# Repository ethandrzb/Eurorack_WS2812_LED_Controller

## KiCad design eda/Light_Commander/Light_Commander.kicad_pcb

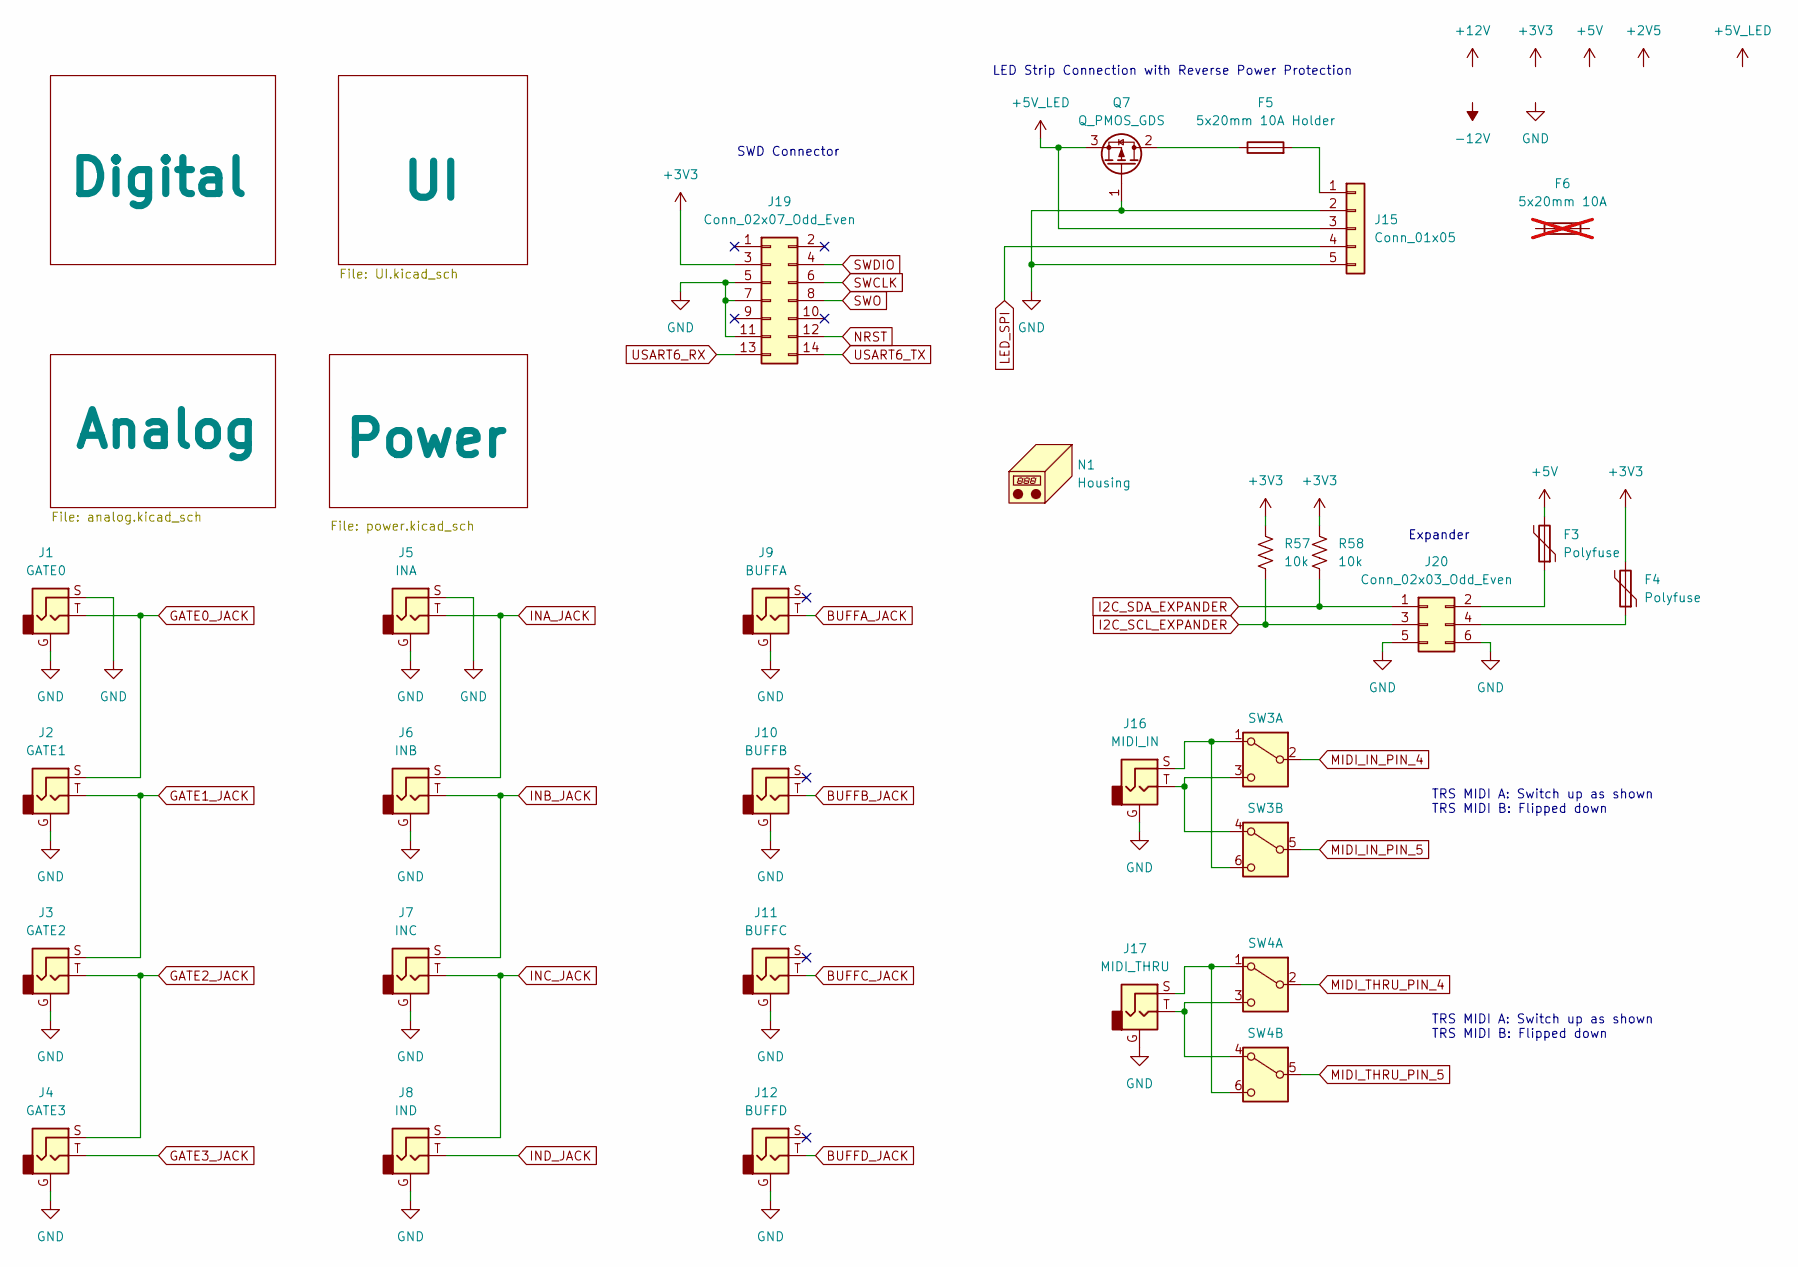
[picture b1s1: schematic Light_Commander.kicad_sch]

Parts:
F3, F4: Polyfuse; Fuse_0805_2012Metric; Digikey_PN 13-SMDH0805B010TFCT-ND
F5: 5x20mm 10A Holder; 05200101Z; Digikey_PN F1504-ND
F6: 5x20mm 10A; Digikey_PN 0617010.MXP-ND; not fitted
J1: GATE0; PJ301M-12
J2: GATE1; PJ301M-12
J3: GATE2; PJ301M-12
J4: GATE3; PJ301M-12
J5: INA; PJ301M-12
J6: INB; PJ301M-12
J7: INC; PJ301M-12
J8: IND; PJ301M-12
J9: BUFFA; PJ301M-12
J10: BUFFB; PJ301M-12
J11: BUFFC; PJ301M-12
J12: BUFFD; PJ301M-12
J15: Conn_01x05; CUI_TBLH10V-350-05BK; Digikey_PN 102-TBLH10V-350-05BK-ND
J16: MIDI_IN; PJ301M-12_STEREO
J17: MIDI_THRU; PJ301M-12_STEREO
J19: Conn_02x07_Odd_Even; SAMTEC_FTSH-107-01-L-DV-K-A; Digikey_PN FTSH-107-01-L-DV-K-A-ND
J20: Conn_02x03_Odd_Even; IDC-Header_2x03_P2.54mm_Vertical; Digikey_PN S9716-ND
N1: Housing; Light_Commander_Panel
Q7: Q_PMOS_GDS; TO-252-2; Digikey_PN 4786-SSFD6909CT-ND
R57, R58: 10k; R_0805_2012Metric; Digikey_PN 311-10.0KCRCT-ND
SW3, SW4: SW_DPDT_x2; CAS-220TA; Digikey_PN CAS220JCT-ND

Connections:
+3V3: F4.2, J19.3, R57.1, R58.1; also elsewhere on the board
+5V: F3.2; also elsewhere on the board
+5V_LED: J15.3, Q7.3 (S); also elsewhere on the board
BUFFA_JACK: J9.T; also elsewhere on the board
BUFFB_JACK: J10.T; also elsewhere on the board
BUFFC_JACK: J11.T; also elsewhere on the board
BUFFD_JACK: J12.T; also elsewhere on the board
GATE0_JACK: J1.T, J2.S; also elsewhere on the board
GATE1_JACK: J2.T, J3.S; also elsewhere on the board
GATE2_JACK: J3.T, J4.S; also elsewhere on the board
GATE3_JACK: J4.T; also elsewhere on the board
GND: J1.G, J1.S, J2.G, J3.G, J4.G, J5.G, J5.S, J6.G, J7.G, J8.G, J9.G, J10.G, J11.G, J12.G, J15.2, J15.5, J16.G, J17.G, J19.5, J19.7, J19.11, J20.5, J20.6, Q7.1 (G); also elsewhere on the board
I2C_SCL_EXPANDER: J20.3, R57.2; also elsewhere on the board
I2C_SDA_EXPANDER: J20.1, R58.2; also elsewhere on the board
INA_JACK: J5.T, J6.S; also elsewhere on the board
INB_JACK: J6.T, J7.S; also elsewhere on the board
INC_JACK: J7.T, J8.S; also elsewhere on the board
IND_JACK: J8.T; also elsewhere on the board
LED_SPI: J15.4; also elsewhere on the board
MIDI_IN_PIN_4: SW3.2 (B); also elsewhere on the board
MIDI_IN_PIN_5: SW3.5 (B); also elsewhere on the board
MIDI_THRU_PIN_4: SW4.2 (B); also elsewhere on the board
MIDI_THRU_PIN_5: SW4.5 (B); also elsewhere on the board
NRST: J19.12; also elsewhere on the board
unnamed: F5.2, J15.1
unnamed: F3.1, J20.2
unnamed: F4.1, J20.4
unnamed: F5.1, Q7.2 (D)
unnamed: J16.S, SW3.1 (A), SW3.6 (C)
unnamed: J16.T, SW3.3 (C), SW3.4 (A)
unnamed: J17.S, SW4.1 (A), SW4.6 (C)
unnamed: J17.T, SW4.3 (C), SW4.4 (A)
SWCLK: J19.6; also elsewhere on the board
SWDIO: J19.4; also elsewhere on the board
SWO: J19.8; also elsewhere on the board
USART6_RX: J19.13; also elsewhere on the board
USART6_TX: J19.14; also elsewhere on the board

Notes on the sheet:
TRS MIDI A: Switch up as shown TRS MIDI B: Flipped down
Expander
SWD Connector
LED Strip Connection with Reverse Power Protection

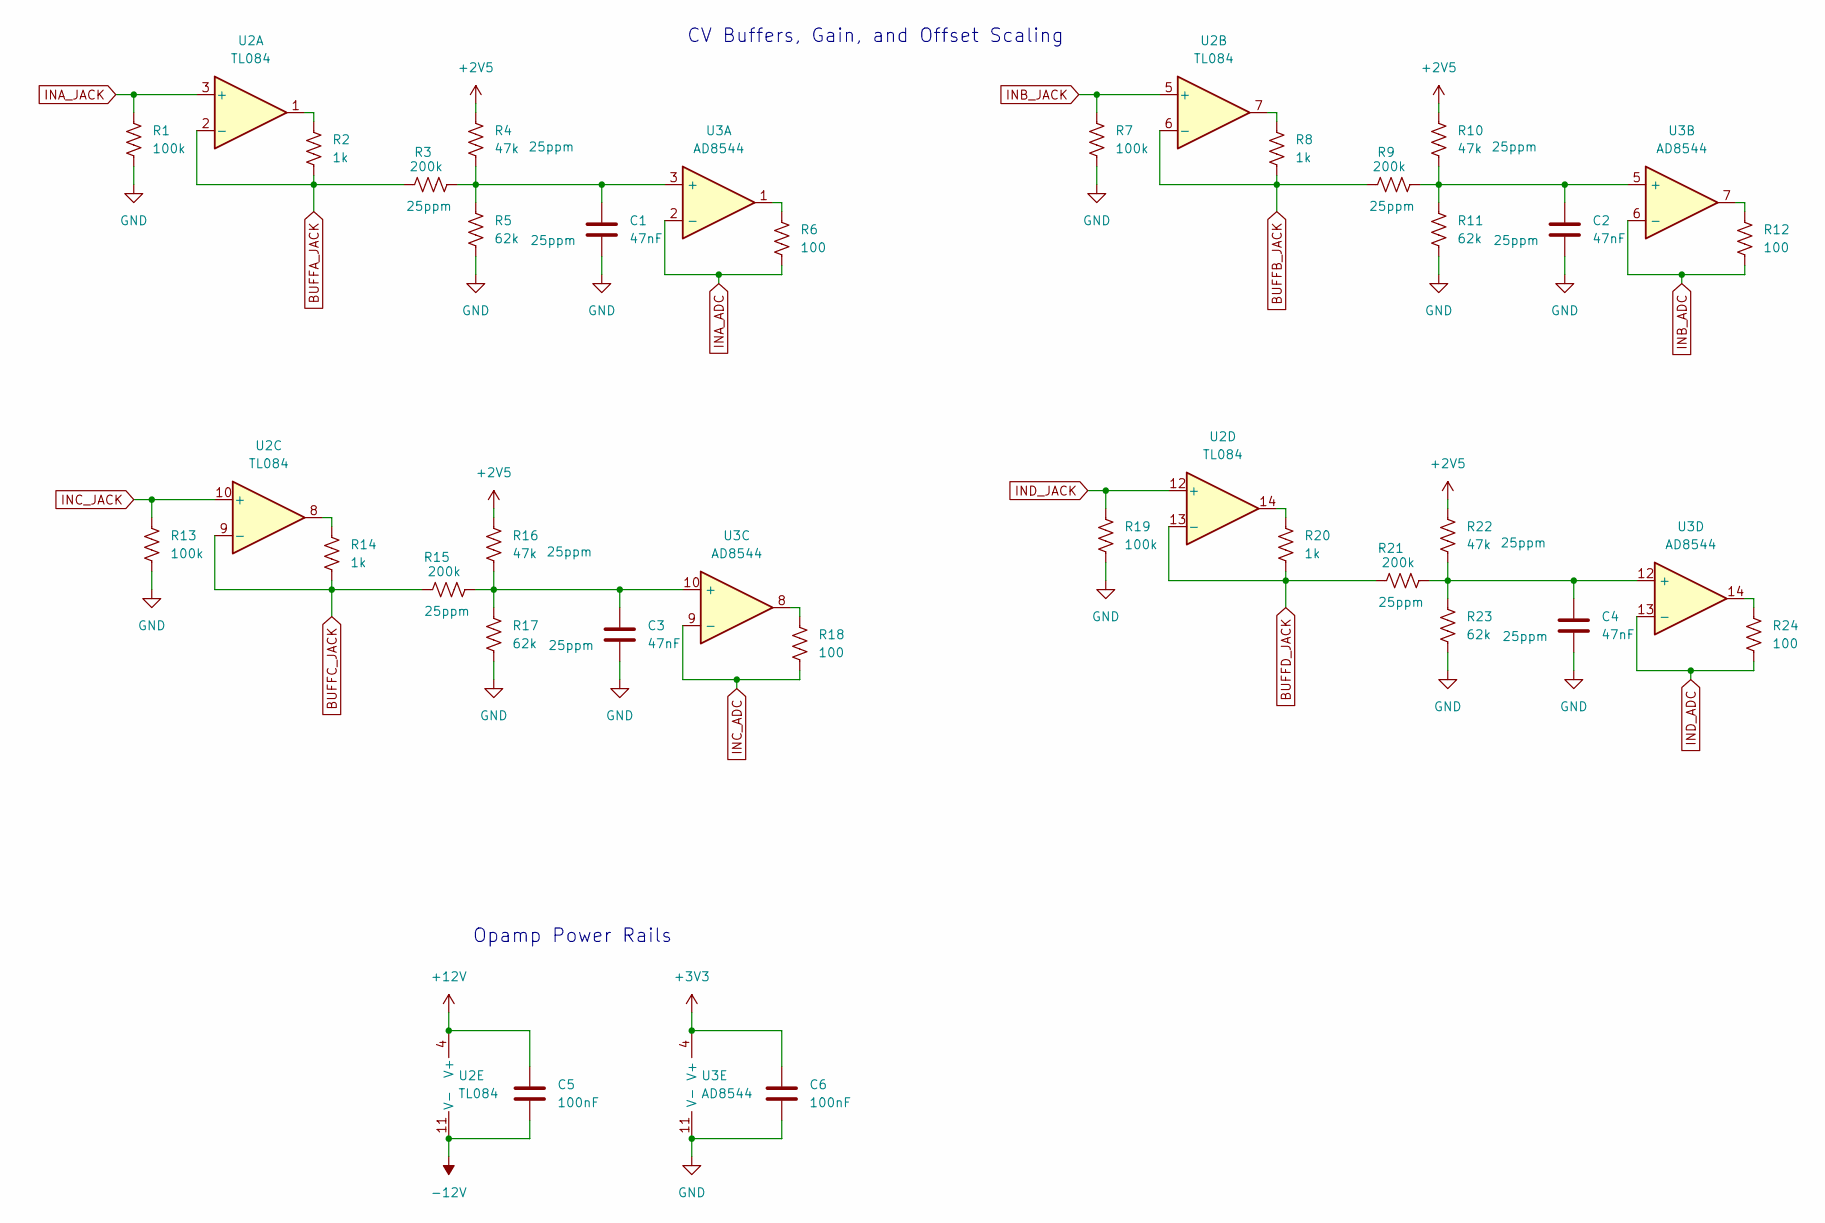
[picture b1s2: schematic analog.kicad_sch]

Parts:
C1, C2, C3, C4: 47nF; C_0805_2012Metric; Digikey_PN 399-C0805C473J3GECTUCT-ND
C5, C6: 100nF; C_0805_2012Metric; Digikey_PN 1276-1003-1-ND
R1, R7, R13, R19: 100k; R_0805_2012Metric; Digikey_PN 311-100KCRCT-ND
R2, R8, R14, R20: 1k; R_0805_2012Metric; Digikey_PN 541-1.00KCCT-ND
R3, R9, R15, R21: 200k; R_0805_2012Metric; Digikey_PN RG20P200KBCT-ND
R4, R10, R16, R22: 47k; R_0805_2012Metric; Digikey_PN RG20P47.0KBCT-ND
R5, R11, R17, R23: 62k; R_0805_2012Metric; Digikey_PN P62KDACT-ND
R6, R12, R18, R24: 100; R_0805_2012Metric; Digikey_PN 311-100CRCT-ND
U2: TL084; SOIC-14_3.9x8.7mm_P1.27mm; Digikey_PN 296-TL084HIDRCT-ND
U3: AD8544; SOIC-14_3.9x8.7mm_P1.27mm; Digikey_PN AD8544ARZ-REELCT-ND

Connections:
+2V5: R4.1, R10.1, R16.1, R22.1; also elsewhere on the board
+3V3: C6.1, U3.4 (V+); also elsewhere on the board
+12V: C5.1, U2.4 (V+); also elsewhere on the board
-12V: C5.2, U2.11 (V-); also elsewhere on the board
BUFFA_JACK: R2.2, R3.1, U2.2 (-); also elsewhere on the board
BUFFB_JACK: R8.2, R9.1, U2.6 (-); also elsewhere on the board
BUFFC_JACK: R14.2, R15.1, U2.9 (-); also elsewhere on the board
BUFFD_JACK: R20.2, R21.1, U2.13 (-); also elsewhere on the board
GND: C1.2, C2.2, C3.2, C4.2, C6.2, R1.2, R5.2, R7.2, R11.2, R13.2, R17.2, R19.2, R23.2, U3.11 (V-); also elsewhere on the board
INA_ADC: R6.1, U3.2 (-); also elsewhere on the board
INA_JACK: R1.1, U2.3 (+); also elsewhere on the board
INB_ADC: R12.1, U3.6 (-); also elsewhere on the board
INB_JACK: R7.1, U2.5 (+); also elsewhere on the board
INC_ADC: R18.1, U3.9 (-); also elsewhere on the board
INC_JACK: R13.1, U2.10 (+); also elsewhere on the board
IND_ADC: R24.1, U3.13 (-); also elsewhere on the board
IND_JACK: R19.1, U2.12 (+); also elsewhere on the board
unnamed: R2.1, U2.1
unnamed: R6.2, U3.1
unnamed: R8.1, U2.7
unnamed: R12.2, U3.7
unnamed: R14.1, U2.8
unnamed: R18.2, U3.8
unnamed: R20.1, U2.14
unnamed: R24.2, U3.14
unnamed: C1.1, R3.2, R4.2, R5.1, U3.3 (+)
unnamed: C2.1, R9.2, R10.2, R11.1, U3.5 (+)
unnamed: C3.1, R15.2, R16.2, R17.1, U3.10 (+)
unnamed: C4.1, R21.2, R22.2, R23.1, U3.12 (+)

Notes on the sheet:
CV Buffers, Gain, and Offset Scaling
Opamp Power Rails

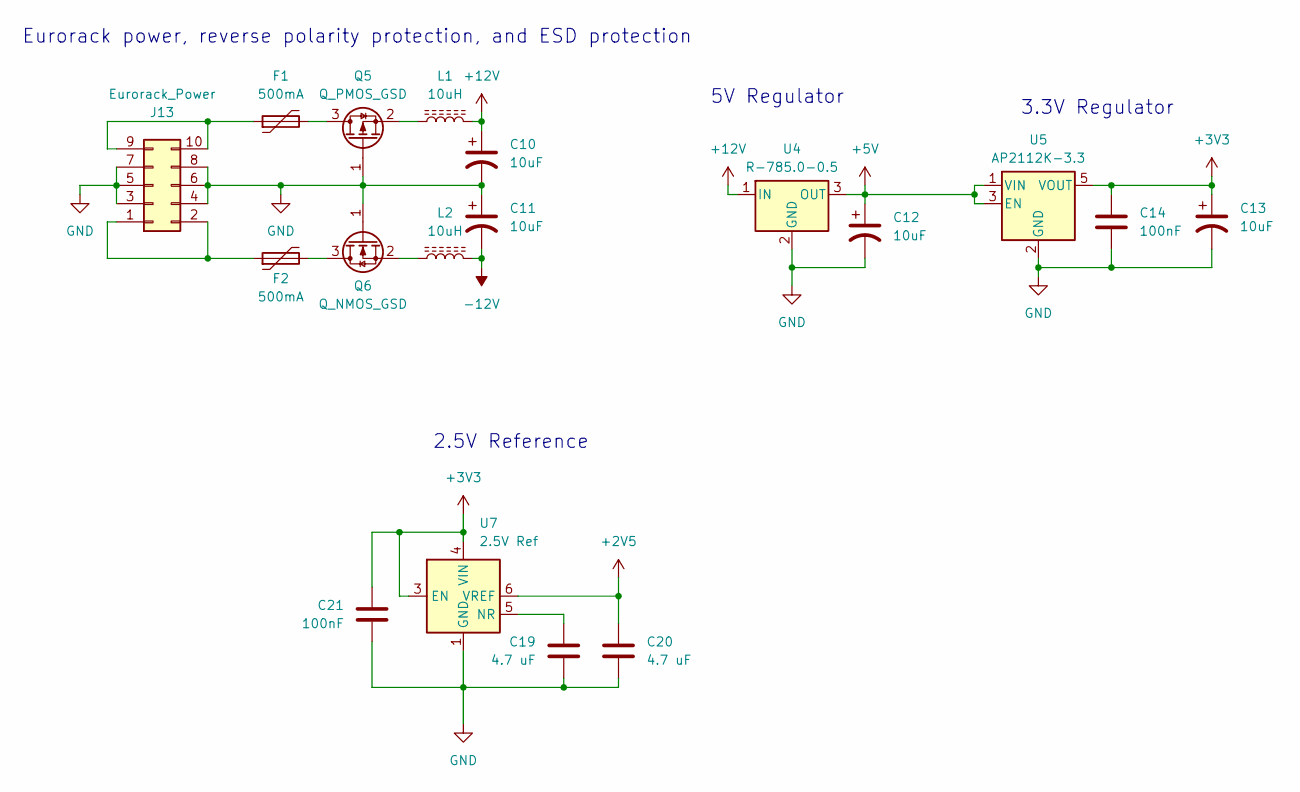
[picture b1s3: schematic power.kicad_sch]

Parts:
C10, C11, C12, C13: 10uF; C_Elec_6.3x7.7; Digikey_PN 732-11937-1-ND
C14, C21: 100nF; C_0805_2012Metric; Digikey_PN 1276-1003-1-ND
C19, C20: 4.7 uF; C_0805_2012Metric; Digikey_PN 1276-1244-1-ND
F1, F2: 500mA; Fuse_1206_3216Metric; Digikey_PN F2110CT-ND
J13: Eurorack_Power; IDC-Header_2x05_P2.54mm_Vertical; Digikey_PN S9169-ND
L1, L2: 10uH; L_1210_3225Metric; Digikey_PN 445-TFM322512ALVA100MTAACT-ND
Q5: Q_PMOS_GSD; SOT-23-3; Digikey_PN 4518-SI2303CT-ND
Q6: Q_NMOS_GSD; SOT-23-3; Digikey_PN 4518-SI2318ACT-ND
U4: R-785.0-0.5; Converter_DCDC_RECOM_R-78E-0.5_THT; Digikey_PN 945-R-78K5.0-0.5-ND
U5: AP2112K-3.3; SOT-23-5; Digikey_PN AP2112K-3.3TRG1DICT-ND
U7: 2.5V Ref; SOT-23-6; Digikey_PN 296-REF35250QDBVRCT-ND

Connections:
+2V5: C20.2, U7.6 (VREF); also elsewhere on the board
+3V3: C13.1, C14.2, C21.2, U5.5 (VOUT), U7.3 (EN), U7.4 (VIN); also elsewhere on the board
+5V: C12.1, U4.3 (OUT), U5.1 (VIN), U5.3 (EN); also elsewhere on the board
+12V: C10.1, L1.2, U4.1 (IN); also elsewhere on the board
-12V: C11.2, L2.2; also elsewhere on the board
GND: C10.2, C11.1, C12.2, C13.2, C14.1, C19.1, C20.1, C21.1, J13.3, J13.4, J13.5, J13.6, J13.7, J13.8, Q5.1 (G), Q6.1 (G), U4.2 (GND), U5.2 (GND), U7.1 (GND), U7.2 (GND); also elsewhere on the board
unnamed: F2.1, J13.1, J13.2
unnamed: F1.1, J13.9, J13.10
unnamed: F1.2, Q5.3 (D)
unnamed: L1.1, Q5.2 (S)
unnamed: F2.2, Q6.3 (D)
unnamed: L2.1, Q6.2 (S)
unnamed: C19.2, U7.5 (NR)

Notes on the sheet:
5V Regulator
2.5V Reference
Eurorack power, reverse polarity protection, and ESD protection
3.3V Regulator

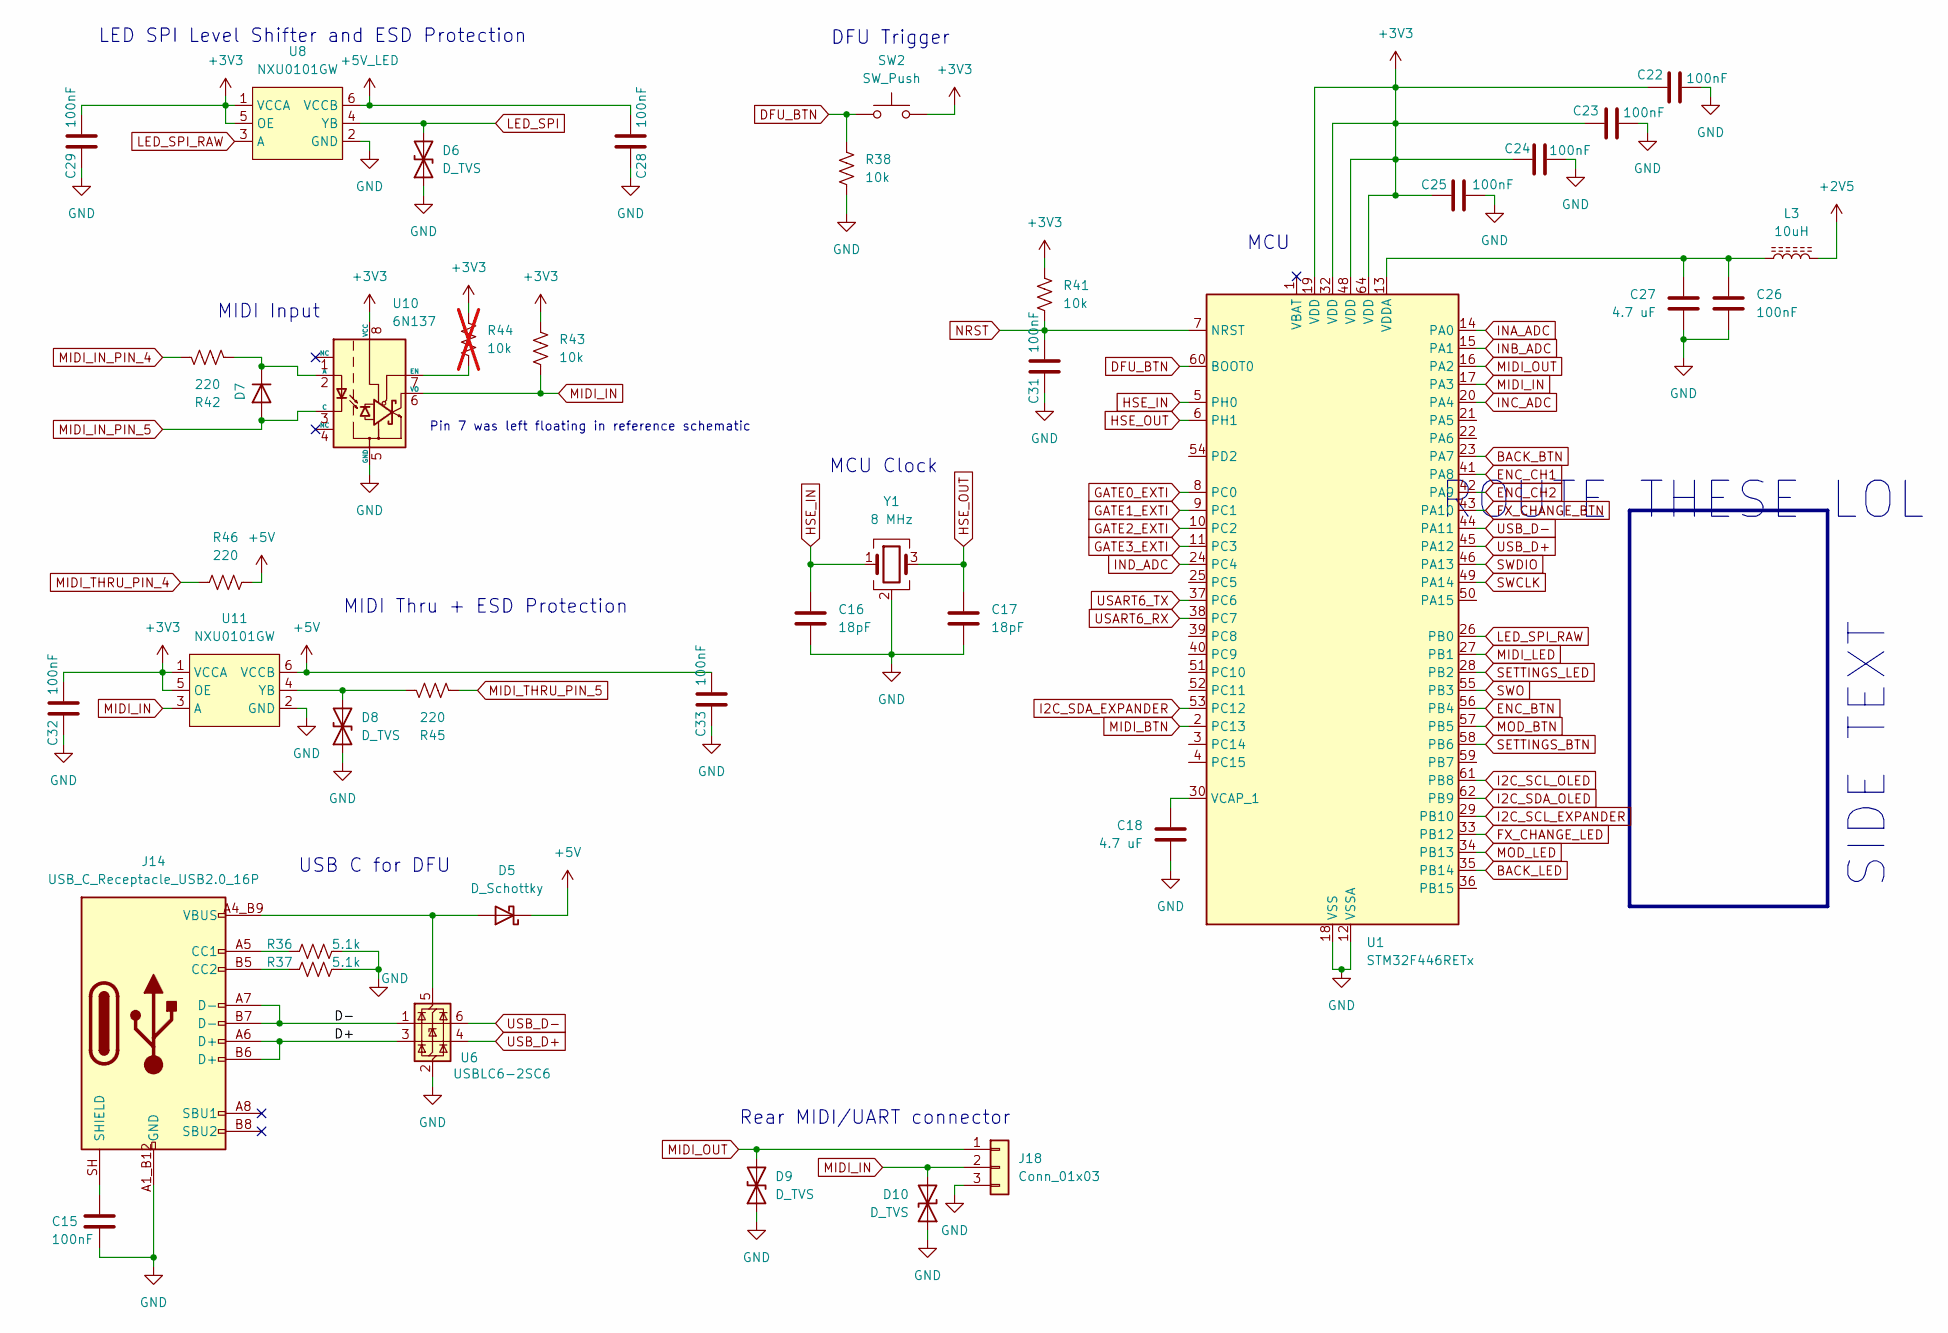
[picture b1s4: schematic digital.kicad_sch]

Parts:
C15, C22, C23, C24, C25, C26, C28, C29, C31, C32, C33: 100nF; C_0805_2012Metric; Digikey_PN 1276-1003-1-ND
C16, C17: 18pF; C_0402_1005Metric; Digikey_PN 490-5858-1-ND
C18, C27: 4.7 uF; C_0805_2012Metric; Digikey_PN 1276-1244-1-ND
D5: D_Schottky; D_SOD-123; Digikey_PN 5399-1N5817WCT-ND
D6, D8, D9, D10: D_TVS; D_SOD-123F; Digikey_PN 4786-GSMF5.0CACT-ND
D7: D; D_SOD-123; Digikey_PN 1N4148WTPMSCT-ND
J14: USB_C_Receptacle_USB2.0_16P; UJ20-C-H-G-SMT-1-P16-TR; Digikey_PN 2223-UJ20-C-H-G-SMT-1-P16-TRCT-ND
J18: Conn_01x03; PinHeader_1x03_P2.54mm_Vertical
L3: 10uH; L_1210_3225Metric; Digikey_PN 445-TFM322512ALVA100MTAACT-ND
R36, R37: 5.1k; R_0805_2012Metric; Digikey_PN 311-5.10KCRCT-ND
R38, R41, R43: 10k; R_0805_2012Metric; Digikey_PN 311-10.0KCRCT-ND
R42, R45, R46: 220; R_0805_2012Metric; Digikey_PN 311-220ARCT-ND
R44: 10k; R_0805_2012Metric; Digikey_PN 311-10.0KCRCT-ND; not fitted
SW2: SW_Push; TS09-63-25-R-160-SMT-TR; Digikey_PN 2223-TS09-63-25-R-260-SMT-TRCT-ND
U1: STM32F446RETx; LQFP-64_10x10mm_P0.5mm; Digikey_PN 497-15376-ND
U6: USBLC6-2SC6; SOT-23-6; Digikey_PN 497-5235-1-ND
U8: NXU0101GW; SOT-363_SC-70-6
U10: 6N137; SOP-8_6.605x9.655mm_P2.54mm; Digikey_PN 58-6N137SMT&RCT-ND
U11: NXU0101GW; SOT-363_SC-70-6; Digikey_PN 1727-NXU0101GWHCT-ND
Y1: 8 MHz; ECS-80-18-33-JGN-TR; Digikey_PN 50-ECS-80-18-33-JGN-CT-ND

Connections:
+2V5: L3.2; also elsewhere on the board
+3V3: C22.2, C23.1, C24.1, C25.2, C29.1, C32.1, R41.1, R43.1, R44.1, SW2.2, U1.19 (VDD), U1.32 (VDD), U1.48 (VDD), U1.64 (VDD), U8.1 (VCCA), U8.5 (OE), U10.8 (VCC), U11.1 (VCCA), U11.5 (OE); also elsewhere on the board
+5V: C33.1, D5.1 (K), R46.1, U11.6 (VCCB); also elsewhere on the board
+5V_LED: C28.1, U8.6 (VCCB); also elsewhere on the board
/Digital/D+: J14.A6 (D+), J14.B6 (D+), U6.3 (I/O2)
/Digital/D-: J14.A7 (D-), J14.B7 (D-), U6.1 (I/O1)
BACK_BTN: U1.23 (PA7); also elsewhere on the board
BACK_LED: U1.35 (PB14); also elsewhere on the board
DFU_BTN: R38.1, SW2.1, U1.60 (BOOT0)
ENC_BTN: U1.56 (PB4); also elsewhere on the board
ENC_CH1: U1.41 (PA8); also elsewhere on the board
ENC_CH2: U1.42 (PA9); also elsewhere on the board
FX_CHANGE_BTN: U1.43 (PA10); also elsewhere on the board
FX_CHANGE_LED: U1.33 (PB12); also elsewhere on the board
GATE0_EXTI: U1.8 (PC0); also elsewhere on the board
GATE1_EXTI: U1.9 (PC1); also elsewhere on the board
GATE2_EXTI: U1.10 (PC2); also elsewhere on the board
GATE3_EXTI: U1.11 (PC3); also elsewhere on the board
GND: C15.2, C16.2, C17.2, C18.1, C22.1, C23.2, C24.2, C25.1, C26.1, C27.1, C28.2, C29.2, C31.2, C32.2, C33.2, D6.1 (A1), D8.1 (A1), D9.1 (A1), D10.1 (A1), J14.A1_B12 (GND), J14.B1_A12 (GND), J18.3, R36.1, R37.1, R38.2, U1.12 (VSSA), U1.18 (VSS), U1.31 (VSS), U1.47 (VSS), U1.63 (VSS), U6.2 (GND), U8.2 (GND), U10.5 (GND), U11.2 (GND), Y1.2 (G), Y1.4 (G); also elsewhere on the board
HSE_IN: C16.1, U1.5 (PH0), Y1.1
HSE_OUT: C17.1, U1.6 (PH1), Y1.3
I2C_SCL_EXPANDER: U1.29 (PB10); also elsewhere on the board
I2C_SCL_OLED: U1.61 (PB8); also elsewhere on the board
I2C_SDA_EXPANDER: U1.53 (PC12); also elsewhere on the board
I2C_SDA_OLED: U1.62 (PB9); also elsewhere on the board
INA_ADC: U1.14 (PA0); also elsewhere on the board
INB_ADC: U1.15 (PA1); also elsewhere on the board
INC_ADC: U1.20 (PA4); also elsewhere on the board
IND_ADC: U1.24 (PC4); also elsewhere on the board
LED_SPI: D6.2 (A2), U8.4 (YB); also elsewhere on the board
LED_SPI_RAW: U1.26 (PB0), U8.3 (A)
MIDI_BTN: U1.2 (PC13); also elsewhere on the board
MIDI_IN: D10.2 (A2), J18.2, R43.2, U1.17 (PA3), U10.6 (VO), U11.3 (A)
MIDI_IN_PIN_4: R42.2; also elsewhere on the board
MIDI_IN_PIN_5: D7.2 (A), U10.3 (C); also elsewhere on the board
MIDI_LED: U1.27 (PB1); also elsewhere on the board
MIDI_OUT: D9.2 (A2), J18.1, U1.16 (PA2)
MIDI_THRU_PIN_4: R46.2; also elsewhere on the board
MIDI_THRU_PIN_5: R45.1; also elsewhere on the board
MOD_BTN: U1.57 (PB5); also elsewhere on the board
MOD_LED: U1.34 (PB13); also elsewhere on the board
NRST: C31.1, R41.2, U1.7 (NRST); also elsewhere on the board
unnamed: D5.2 (A), J14.A4_B9 (VBUS), J14.B4_A9 (VBUS), U6.5 (VBUS)
unnamed: D7.1 (K), R42.1, U10.2 (A)
unnamed: D8.2 (A2), R45.2, U11.4 (YB)
unnamed: J14.A5 (CC1), R36.2
unnamed: J14.B5 (CC2), R37.2
unnamed: C15.1, J14.SH (SHIELD)
unnamed: C18.2, U1.30 (VCAP_1)
unnamed: C26.2, C27.2, L3.1, U1.13 (VDDA)
unnamed: R44.2, U10.7 (EN)
SETTINGS_BTN: U1.58 (PB6); also elsewhere on the board
SETTINGS_LED: U1.28 (PB2); also elsewhere on the board
SWCLK: U1.49 (PA14); also elsewhere on the board
SWDIO: U1.46 (PA13); also elsewhere on the board
SWO: U1.55 (PB3); also elsewhere on the board
USART6_RX: U1.38 (PC7); also elsewhere on the board
USART6_TX: U1.37 (PC6); also elsewhere on the board
USB_D+: U1.45 (PA12), U6.4 (I/O2)
USB_D-: U1.44 (PA11), U6.6 (I/O1)

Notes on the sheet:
Rear MIDI/UART connector
MCU
MIDI Input
USB C for DFU
SIDE TEXT
MCU Clock
MIDI Thru + ESD Protection
DFU Trigger
Pin 7 was left floating in reference schematic
ROUTE THESE LOL
LED SPI Level Shifter and ESD Protection

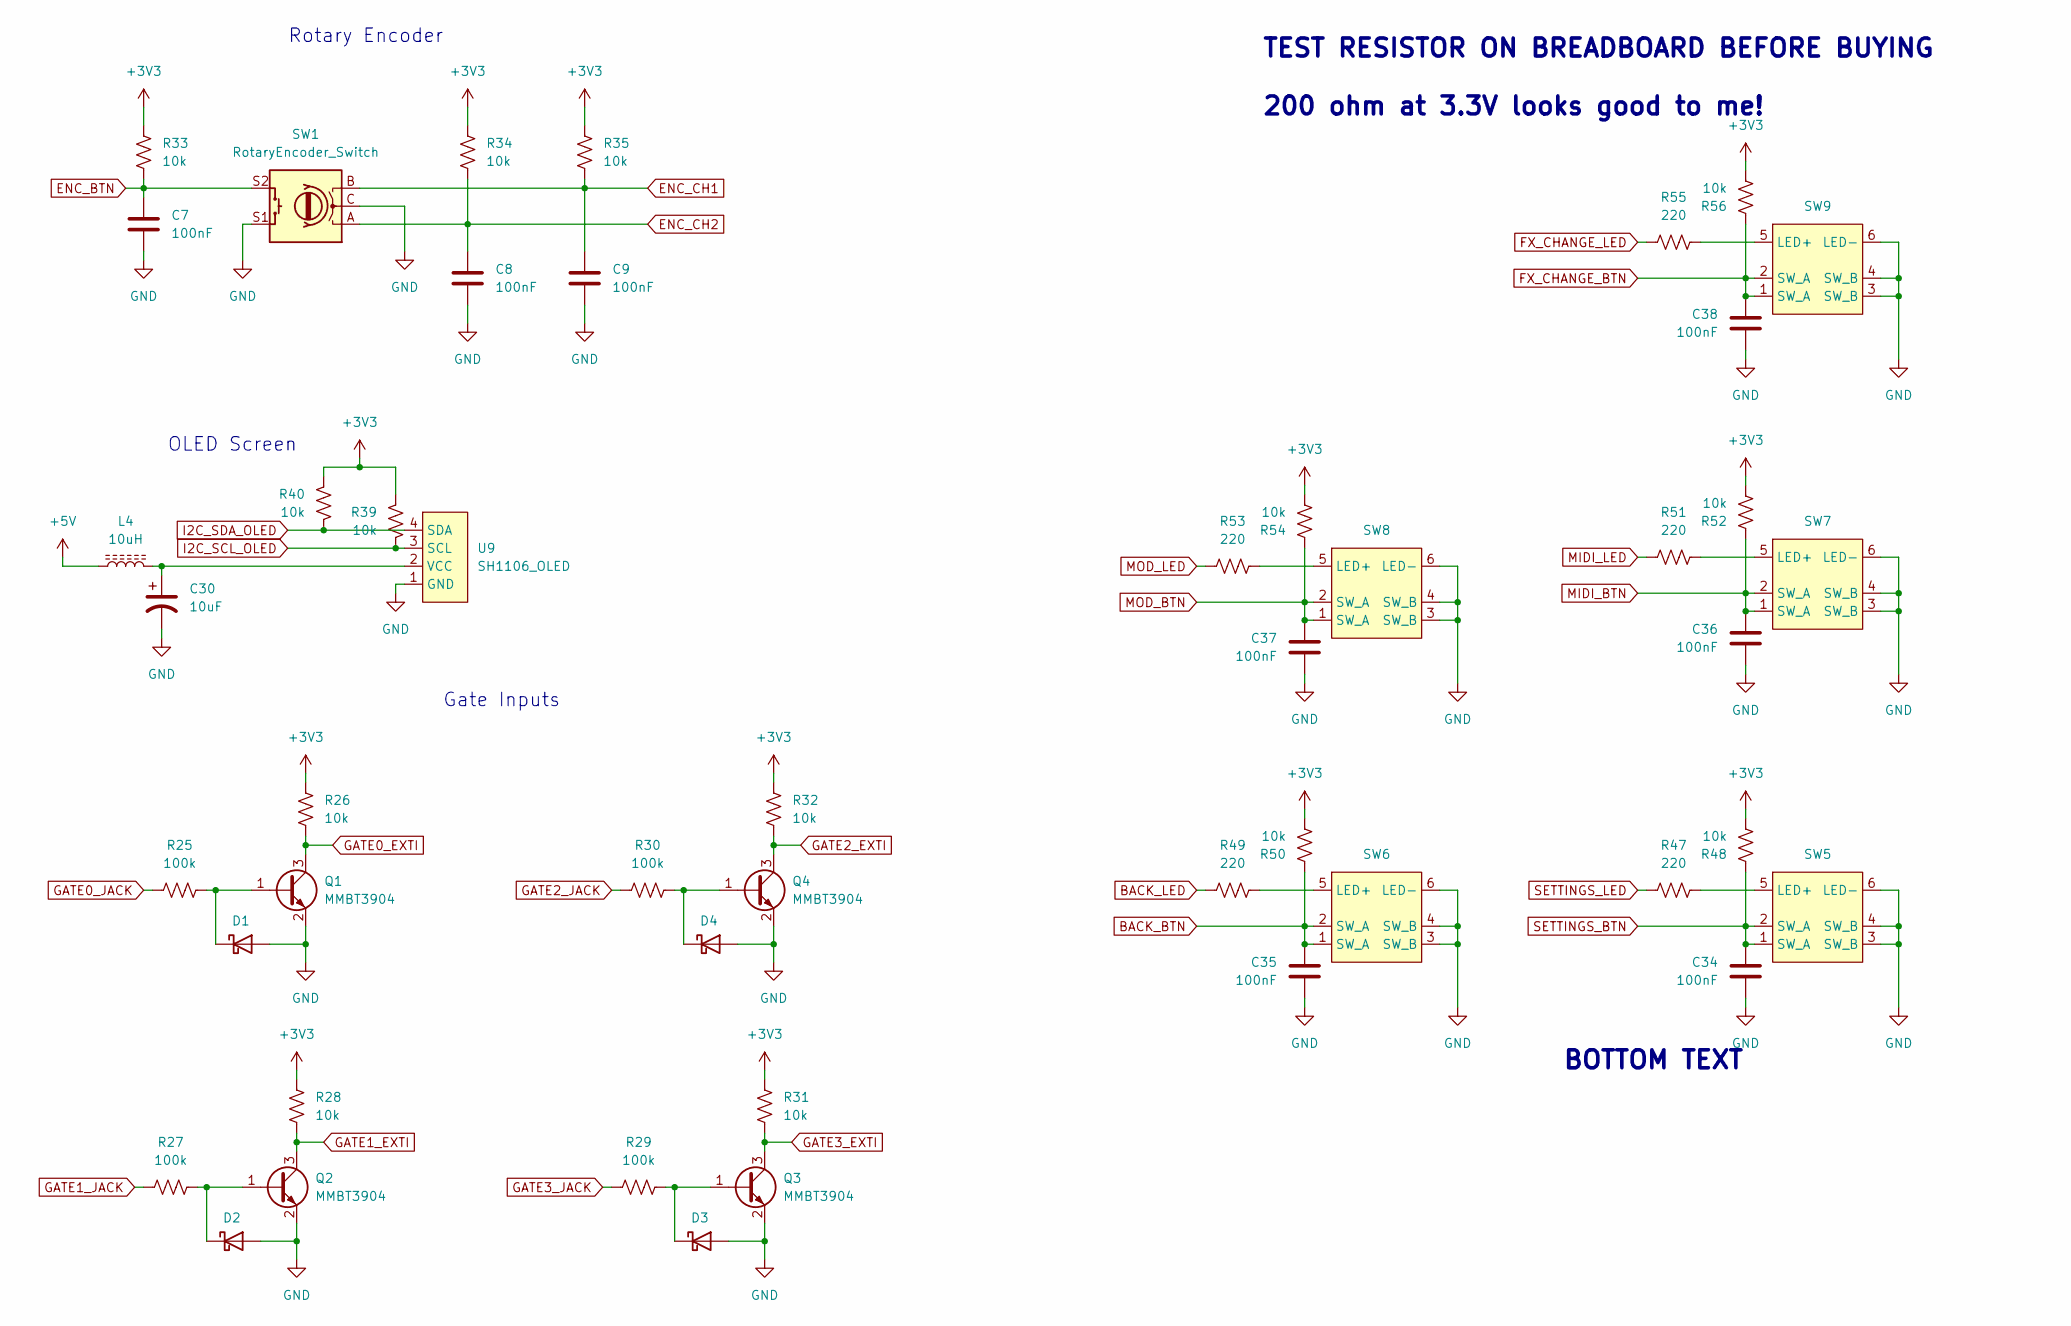
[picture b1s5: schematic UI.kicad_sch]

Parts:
C7, C8, C9, C34, C35, C36, C37, C38: 100nF; C_0805_2012Metric; Digikey_PN 1276-1003-1-ND
C30: 10uF; C_Elec_6.3x7.7; Digikey_PN 732-11937-1-ND
D1, D2, D3, D4: GSBAT54W; D_SOD-123; Digikey_PN 4786-GSBAT54WCT-ND
L4: 10uH; L_1210_3225Metric; Digikey_PN 445-TFM322512ALVA100MTAACT-ND
Q1, Q2, Q3, Q4: MMBT3904; SOT-23; Digikey_PN 4786-MMBT3904CT-ND
R25, R27, R29, R30: 100k; R_0805_2012Metric; Digikey_PN 311-100KCRCT-ND
R26, R28, R31, R32, R33, R34, R35, R39, R40, R48, R50, R52, R54, R56: 10k; R_0805_2012Metric; Digikey_PN 311-10.0KCRCT-ND
R47, R49, R51, R53, R55: 220; R_0805_2012Metric; Digikey_PN 311-220ARCT-ND
SW1: RotaryEncoder_Switch; PEC11R-4220K-S0024; Digikey_PN PEC11R-4220K-S0024-ND
SW5, SW6, SW7, SW8, SW9: SW_Tact_Low_Profile_LED_ExtraHoles
U9: SH1106_OLED; SH1106_1.3in_OLED

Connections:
+3V3: R26.1, R28.1, R31.1, R32.1, R33.1, R34.1, R35.1, R39.1, R40.1, R48.2, R50.2, R52.2, R54.2, R56.2; also elsewhere on the board
+5V: L4.1; also elsewhere on the board
BACK_BTN: C35.1, R50.1, SW6.1 (SW_A), SW6.2 (SW_A); also elsewhere on the board
BACK_LED: R49.2; also elsewhere on the board
ENC_BTN: C7.1, R33.2, SW1.S2; also elsewhere on the board
ENC_CH1: C9.1, R35.2, SW1.B; also elsewhere on the board
ENC_CH2: C8.1, R34.2, SW1.A; also elsewhere on the board
FX_CHANGE_BTN: C38.1, R56.1, SW9.1 (SW_A), SW9.2 (SW_A); also elsewhere on the board
FX_CHANGE_LED: R55.2; also elsewhere on the board
GATE0_EXTI: Q1.3 (C), R26.2; also elsewhere on the board
GATE0_JACK: R25.1; also elsewhere on the board
GATE1_EXTI: Q2.3 (C), R28.2; also elsewhere on the board
GATE1_JACK: R27.1; also elsewhere on the board
GATE2_EXTI: Q4.3 (C), R32.2; also elsewhere on the board
GATE2_JACK: R30.1; also elsewhere on the board
GATE3_EXTI: Q3.3 (C), R31.2; also elsewhere on the board
GATE3_JACK: R29.1; also elsewhere on the board
GND: C7.2, C8.2, C9.2, C30.2, C34.2, C35.2, C36.2, C37.2, C38.2, D1.2 (A), D2.2 (A), D3.2 (A), D4.2 (A), Q1.2 (E), Q2.2 (E), Q3.2 (E), Q4.2 (E), SW1.C, SW1.S1, SW5.3 (SW_B), SW5.4 (SW_B), SW5.6 (LED-), SW6.3 (SW_B), SW6.4 (SW_B), SW6.6 (LED-), SW7.3 (SW_B), SW7.4 (SW_B), SW7.6 (LED-), SW8.3 (SW_B), SW8.4 (SW_B), SW8.6 (LED-), SW9.3 (SW_B), SW9.4 (SW_B), SW9.6 (LED-), U9.1 (GND); also elsewhere on the board
I2C_SCL_OLED: R39.2, U9.3 (SCL); also elsewhere on the board
I2C_SDA_OLED: R40.2, U9.4 (SDA); also elsewhere on the board
MIDI_BTN: C36.1, R52.1, SW7.1 (SW_A), SW7.2 (SW_A); also elsewhere on the board
MIDI_LED: R51.2; also elsewhere on the board
MOD_BTN: C37.1, R54.1, SW8.1 (SW_A), SW8.2 (SW_A); also elsewhere on the board
MOD_LED: R53.2; also elsewhere on the board
unnamed: D1.1 (K), Q1.1 (B), R25.2
unnamed: D2.1 (K), Q2.1 (B), R27.2
unnamed: D3.1 (K), Q3.1 (B), R29.2
unnamed: D4.1 (K), Q4.1 (B), R30.2
unnamed: R47.1, SW5.5 (LED+)
unnamed: R49.1, SW6.5 (LED+)
unnamed: R51.1, SW7.5 (LED+)
unnamed: R53.1, SW8.5 (LED+)
unnamed: R55.1, SW9.5 (LED+)
unnamed: C30.1, L4.2, U9.2 (VCC)
SETTINGS_BTN: C34.1, R48.1, SW5.1 (SW_A), SW5.2 (SW_A); also elsewhere on the board
SETTINGS_LED: R47.2; also elsewhere on the board

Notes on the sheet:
BOTTOM TEXT
OLED Screen
Rotary Encoder
TEST RESISTOR ON BREADBOARD BEFORE BUYING 200 ohm at 3.3V looks good to me!
Gate Inputs

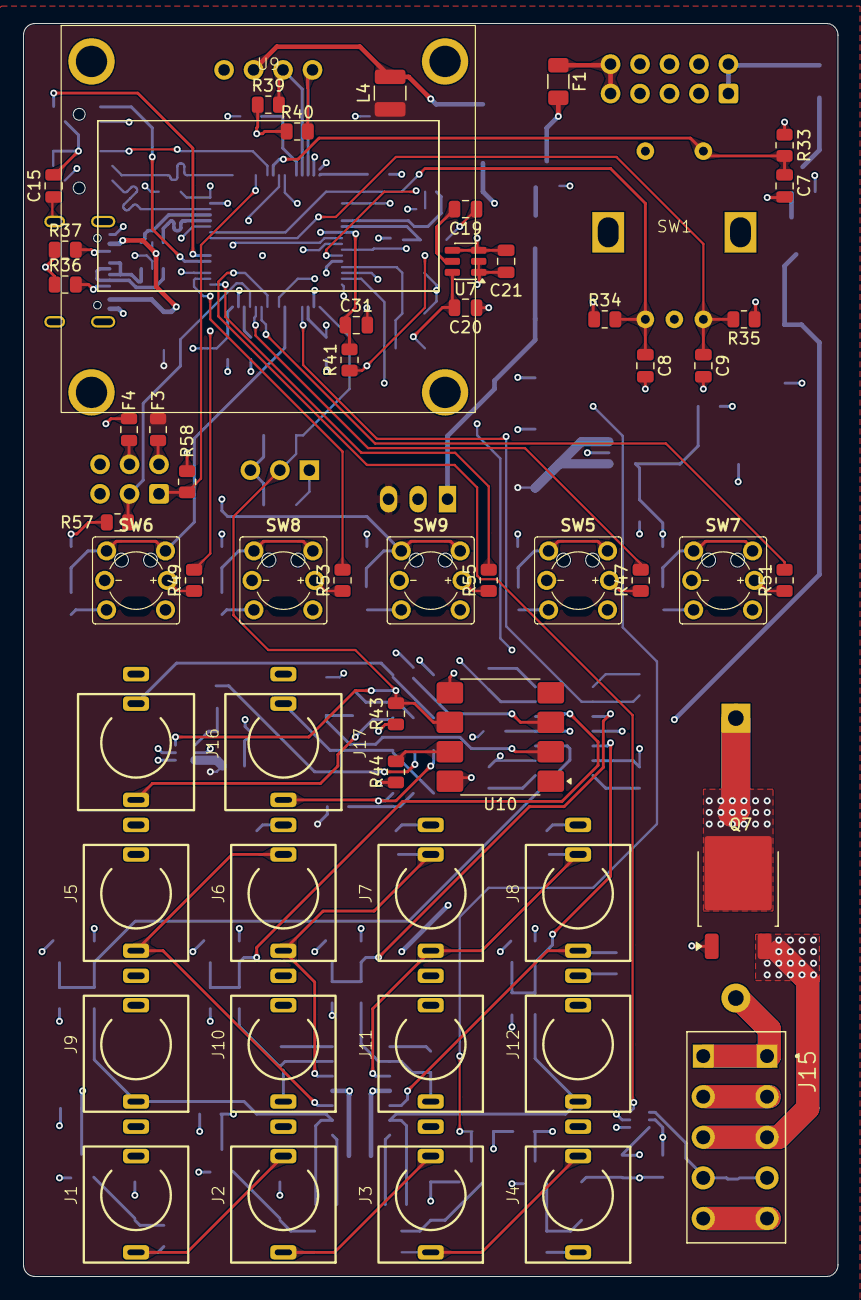
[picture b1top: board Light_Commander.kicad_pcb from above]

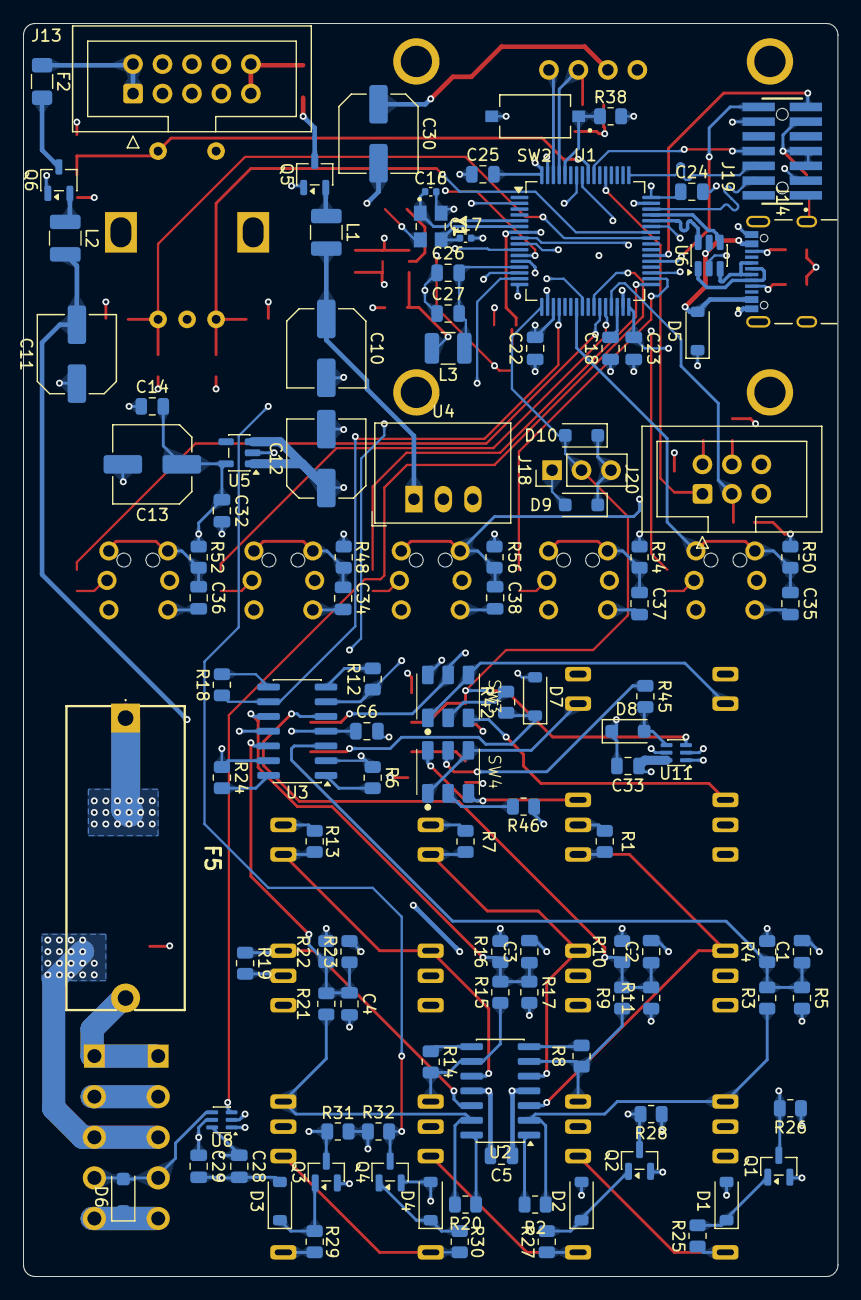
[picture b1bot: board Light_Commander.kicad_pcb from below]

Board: 6 copper layers, 70.2 x 108.0 mm, 164 parts (109 on the bottom side), 111 nets.
